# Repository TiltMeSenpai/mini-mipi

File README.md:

# mini-mipi
hi github actions (I just needed to kick the plotter script)

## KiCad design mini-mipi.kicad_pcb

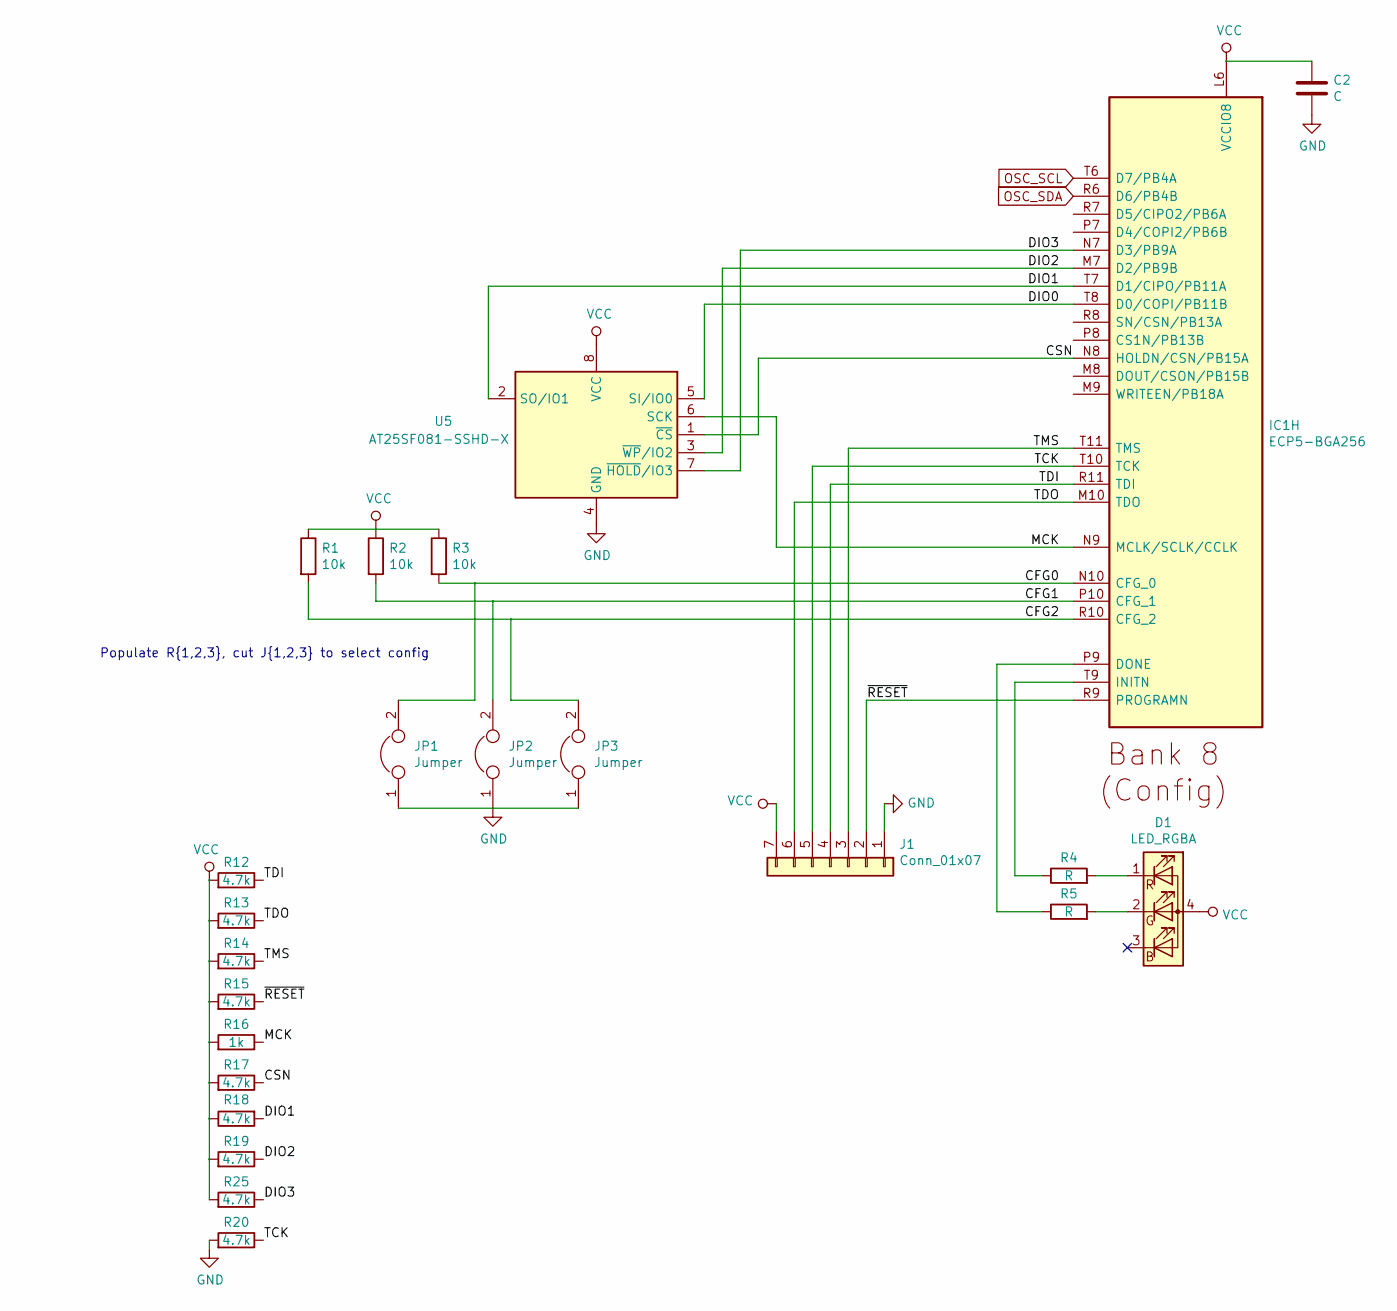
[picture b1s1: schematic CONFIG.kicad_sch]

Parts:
C2: C; C_0402_1005Metric
D1: LED_RGBA; LED_0404
IC1: ECP5-BGA256; BGA256C80P16X16_1400X1400X170; Manufacturer_Part_Number LFE5U-12F-6BG256C; Mouser Part Number 842-LFE5U12F6BG256C
J1: Conn_01x07; PinHeader_1x07_P2.54mm_Vertical
JP1, JP2, JP3: Jumper; SolderJumper-2_P1.3mm_Bridged_RoundedPad1.0x1.5mm
R1, R2, R3: 10k; R_0402_1005Metric
R4, R5: R; R_0402_1005Metric
R12, R13, R14, R15, R17, R18, R19, R20, R25: 4.7k; R_0402_1005Metric
R16: 1k; R_0402_1005Metric
U5: AT25SF081-SSHD-X; SOIC-8_5.275x5.275mm_P1.27mm

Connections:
/CONFIG/CFG0: IC1.N10 (CFG_0), JP1.2, R3.2
/CONFIG/CFG1: IC1.P10 (CFG_1), JP2.2, R2.2
/CONFIG/CFG2: IC1.R10 (CFG_2), JP3.2, R1.2
/CONFIG/CSN: IC1.N8 (HOLDN/CSN/PB15A), R17.1, U5.1 (~CS)
/CONFIG/DIO0: IC1.T8 (D0/COPI/PB11B), U5.5 (SI/IO0)
/CONFIG/DIO1: IC1.T7 (D1/CIPO/PB11A), R18.2, U5.2 (SO/IO1)
/CONFIG/DIO2: IC1.M7 (D2/PB9B), R19.1, U5.3 (~WP~/IO2)
/CONFIG/DIO3: IC1.N7 (D3/PB9A), R25.1, U5.7 (~HOLD~/IO3)
/CONFIG/MCK: IC1.N9 (MCLK/SCLK/CCLK), R16.1, U5.6 (SCK)
/CONFIG/TCK: IC1.T10 (TCK), J1.5, R20.1
/CONFIG/TDI: IC1.R11 (TDI), J1.4, R12.1
/CONFIG/TDO: IC1.M10 (TDO), J1.6, R13.1
/CONFIG/TMS: IC1.T11 (TMS), J1.3, R14.1
/CONFIG/~RESET: IC1.R9 (PROGRAMN), J1.2, R15.1
GND: C2.2, J1.1, JP1.1, JP2.1, JP3.1, R20.2, U5.4 (GND); also elsewhere on the board
unnamed: D1.1 (RK), R4.2
unnamed: D1.2 (GK), R5.2
unnamed: IC1.P9 (DONE), R5.1
unnamed: IC1.T9 (INITN), R4.1
OSC_SCL: IC1.T6 (D7/PB4A); also elsewhere on the board
OSC_SDA: IC1.R6 (D6/PB4B); also elsewhere on the board
VCC: C2.1, D1.4 (A), IC1.L6 (VCCIO8), J1.7, R1.1, R2.1, R3.1, R12.2, R13.2, R14.2, R15.2, R16.2, R17.2, R18.1, R19.2, R25.2, U5.8 (VCC); also elsewhere on the board

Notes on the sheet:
Populate R{1,2,3}, cut J{1,2,3} to select config

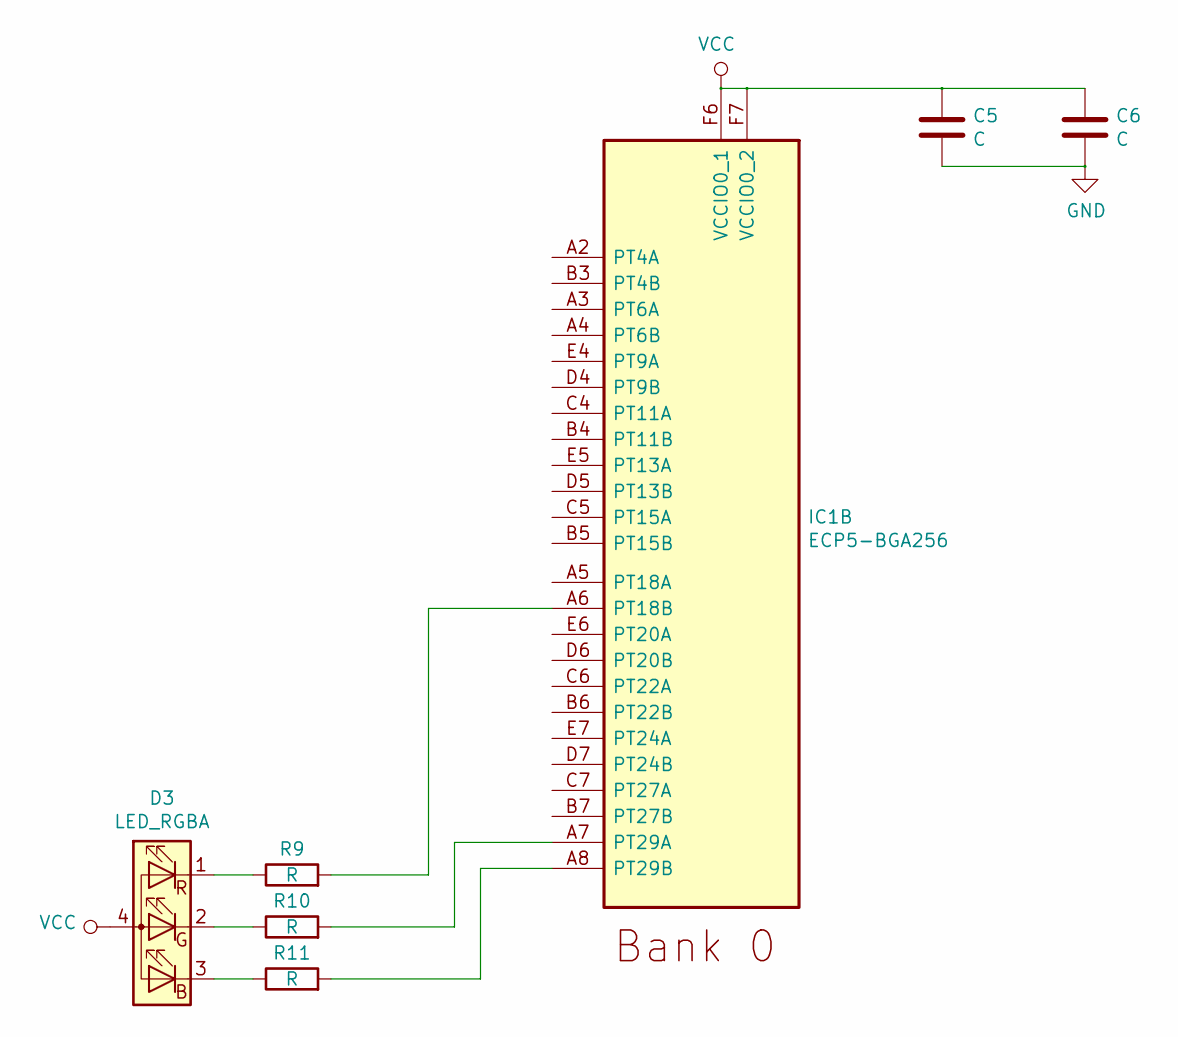
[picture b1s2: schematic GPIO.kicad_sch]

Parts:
C5, C6: C; C_0402_1005Metric
D3: LED_RGBA; LED_0404
IC1: ECP5-BGA256; BGA256C80P16X16_1400X1400X170; Manufacturer_Part_Number LFE5U-12F-6BG256C; Mouser Part Number 842-LFE5U12F6BG256C
R9, R10, R11: R; R_0402_1005Metric

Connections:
GND: C5.2, C6.2; also elsewhere on the board
unnamed: D3.1 (RK), R9.1
unnamed: D3.2 (GK), R10.1
unnamed: D3.3 (BK), R11.1
unnamed: IC1.A6 (PT18B), R9.2
unnamed: IC1.A7 (PT29A), R10.2
unnamed: IC1.A8 (PT29B), R11.2
VCC: C5.1, C6.1, D3.4 (A), IC1.F6 (VCCIO0_1), IC1.F7 (VCCIO0_2); also elsewhere on the board

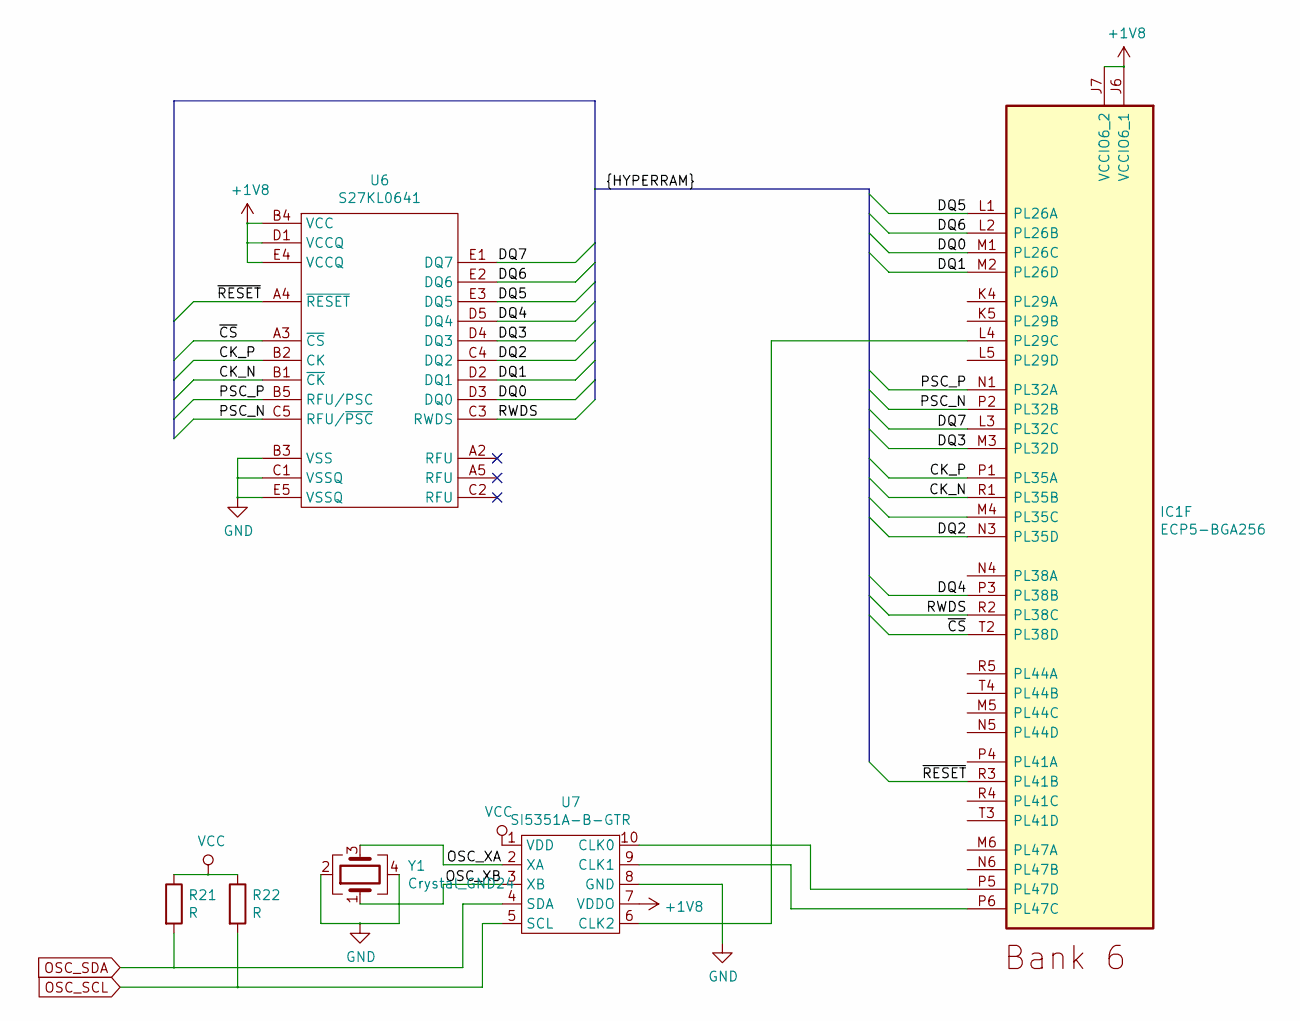
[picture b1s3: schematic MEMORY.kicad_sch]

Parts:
IC1: ECP5-BGA256; BGA256C80P16X16_1400X1400X170; Manufacturer_Part_Number LFE5U-12F-6BG256C; Mouser Part Number 842-LFE5U12F6BG256C
R21, R22: R; R_0402_1005Metric
U6: S27KL0641; BGA-24_5x5_6.0x8.0mm
U7: SI5351A-B-GTR; MSOP-10_3x3mm_P0.5mm
Y1: Crystal_GND24; Crystal_SMD_2016-4Pin_2.0x1.6mm

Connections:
+1V8: IC1.J6 (VCCIO6_1), IC1.J7 (VCCIO6_2), U6.B4 (VCC), U6.D1 (VCCQ), U6.E4 (VCCQ), U7.7 (VDDO); also elsewhere on the board
/MEMORY/CK_N: IC1.R1 (PL35B), U6.B1 (~CK)
/MEMORY/CK_P: IC1.P1 (PL35A), U6.B2 (CK)
/MEMORY/DQ0: IC1.M1 (PL26C), U6.D3 (DQ0)
/MEMORY/DQ1: IC1.M2 (PL26D), U6.D2 (DQ1)
/MEMORY/DQ2: IC1.N3 (PL35D), U6.C4 (DQ2)
/MEMORY/DQ3: IC1.M3 (PL32D), U6.D4 (DQ3)
/MEMORY/DQ4: IC1.P3 (PL38B), U6.D5 (DQ4)
/MEMORY/DQ5: IC1.L1 (PL26A), U6.E3 (DQ5)
/MEMORY/DQ6: IC1.L2 (PL26B), U6.E2 (DQ6)
/MEMORY/DQ7: IC1.L3 (PL32C), U6.E1 (DQ7)
/MEMORY/OSC_XA: U7.2 (XA), Y1.3
/MEMORY/OSC_XB: U7.3 (XB), Y1.1
/MEMORY/PSC_N: IC1.P2 (PL32B), U6.C5 (RFU/~PSC)
/MEMORY/PSC_P: IC1.N1 (PL32A), U6.B5 (RFU/PSC)
/MEMORY/RWDS: IC1.R2 (PL38C), U6.C3 (RWDS)
/MEMORY/~CS: IC1.T2 (PL38D), U6.A3 (~CS)
/MEMORY/~RESET: IC1.R3 (PL41B), U6.A4 (~RESET)
GND: U6.B3 (VSS), U6.C1 (VSSQ), U6.E5 (VSSQ), U7.8 (GND), Y1.2, Y1.4; also elsewhere on the board
unnamed: IC1.L4 (PL29C), U7.6 (CLK2)
unnamed: IC1.P5 (PL47D), U7.10 (CLK0)
unnamed: IC1.P6 (PL47C), U7.9 (CLK1)
OSC_SCL: R22.2, U7.5 (SCL); also elsewhere on the board
OSC_SDA: R21.2, U7.4 (SDA); also elsewhere on the board
VCC: R21.1, R22.1, U7.1 (VDD); also elsewhere on the board

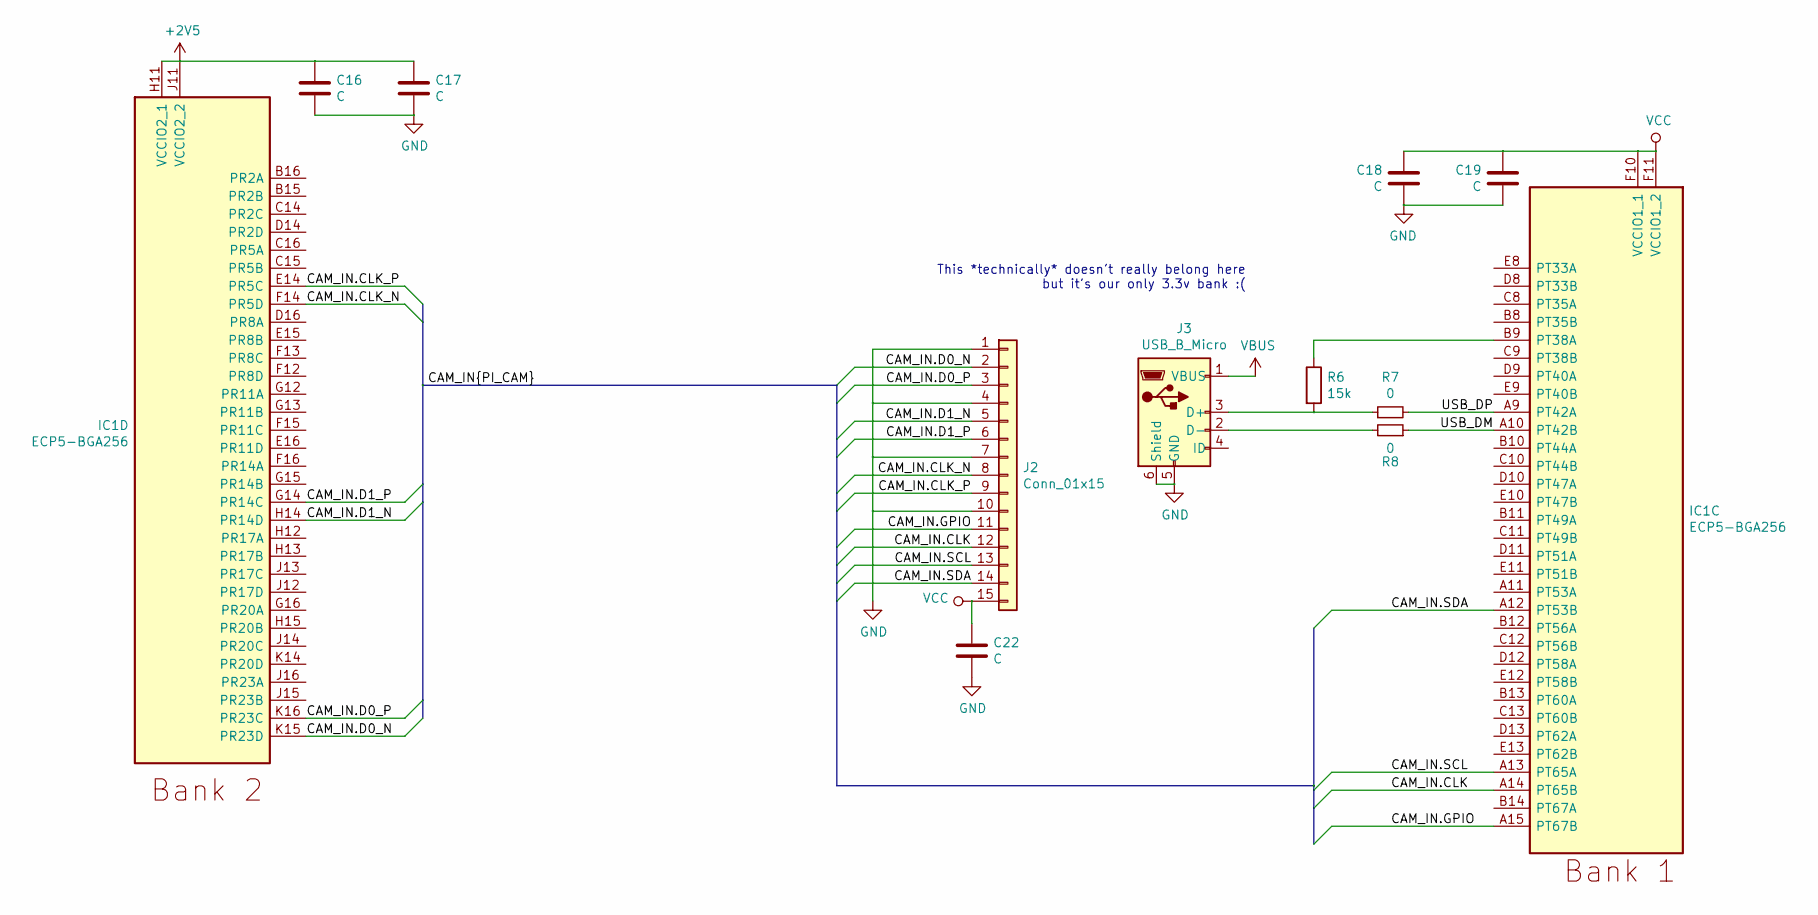
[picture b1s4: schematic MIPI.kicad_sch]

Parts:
C16, C17, C18, C19: C; C_0402_1005Metric
C22: C; C_0805_2012Metric
IC1: ECP5-BGA256; BGA256C80P16X16_1400X1400X170; Manufacturer_Part_Number LFE5U-12F-6BG256C; Mouser Part Number 842-LFE5U12F6BG256C
J2: Conn_01x15; AMPHENOL_SFW15R-1STE1LF
J3: USB_B_Micro; USB_Micro-B_Wuerth_629105150521
R6: 15k; R_0402_1005Metric
R7, R8: 0; R_0402_1005Metric

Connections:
+2V5: C16.1, C17.1, IC1.H11 (VCCIO2_1), IC1.J11 (VCCIO2_2); also elsewhere on the board
/MIPI/CAM_IN.CLK: IC1.A14 (PT65B), J2.12
/MIPI/CAM_IN.CLK_N: IC1.F14 (PR5D), J2.8
/MIPI/CAM_IN.CLK_P: IC1.E14 (PR5C), J2.9
/MIPI/CAM_IN.D0_N: IC1.K15 (PR23D), J2.2
/MIPI/CAM_IN.D0_P: IC1.K16 (PR23C), J2.3
/MIPI/CAM_IN.D1_N: IC1.H14 (PR14D), J2.5
/MIPI/CAM_IN.D1_P: IC1.G14 (PR14C), J2.6
/MIPI/CAM_IN.GPIO: IC1.A15 (PT67B), J2.11
/MIPI/CAM_IN.SCL: IC1.A13 (PT65A), J2.13
/MIPI/CAM_IN.SDA: IC1.A12 (PT53B), J2.14
/MIPI/USB_DM: IC1.A10 (PT42B), R8.1
/MIPI/USB_DP: IC1.A9 (PT42A), R7.2
GND: C16.2, C17.2, C18.2, C19.2, C22.2, J2.1, J2.4, J2.7, J2.10, J3.5 (GND), J3.6 (Shield); also elsewhere on the board
unnamed: IC1.B9 (PT38A), R6.1
unnamed: J3.2 (D-), R8.2
unnamed: J3.3 (D+), R6.2, R7.1
VBUS: J3.1 (VBUS); also elsewhere on the board
VCC: C18.1, C19.1, C22.1, IC1.F10 (VCCIO1_1), IC1.F11 (VCCIO1_2), J2.15; also elsewhere on the board

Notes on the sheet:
This *technically* doesn't really belong here but it's our only 3.3v bank :(

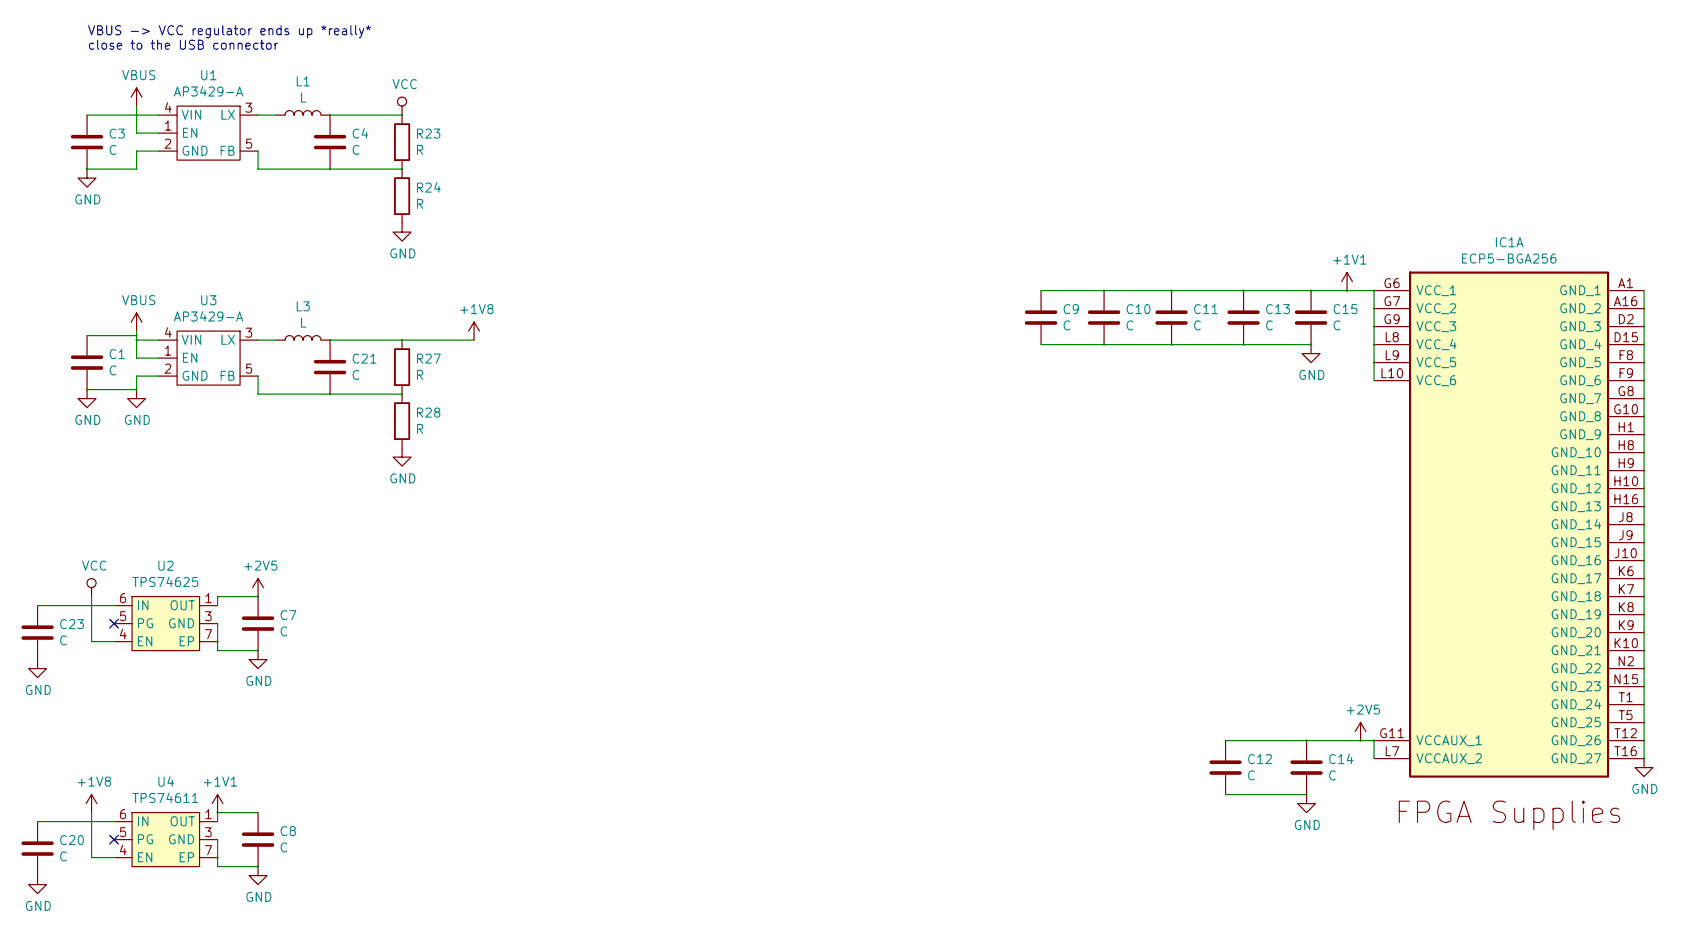
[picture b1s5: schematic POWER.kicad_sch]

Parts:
C1, C3, C7, C8, C20, C23: C; C_0805_2012Metric
C4, C9, C10, C11, C12, C13, C14, C15, C21: C; C_0402_1005Metric
IC1: ECP5-BGA256; BGA256C80P16X16_1400X1400X170; Manufacturer_Part_Number LFE5U-12F-6BG256C; Mouser Part Number 842-LFE5U12F6BG256C
L1, L3: L; L_1210_3225Metric
R23, R24, R27, R28: R; R_0402_1005Metric
U1, U3: AP3429-A; TSOT-23-5
U2: TPS74625; WSON-6-1EP_2x2mm_P0.65mm_EP1x1.6mm
U4: TPS74611; WSON-6-1EP_2x2mm_P0.65mm_EP1x1.6mm

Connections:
+1V1: C8.1, C9.1, C10.1, C11.1, C13.1, C15.1, IC1.G6 (VCC_1), IC1.G7 (VCC_2), IC1.G9 (VCC_3), IC1.L8 (VCC_4), IC1.L9 (VCC_5), IC1.L10 (VCC_6), U4.1 (OUT)
+1V8: C20.1, C21.1, L3.2, R27.1, U4.4 (EN), U4.6 (IN); also elsewhere on the board
+2V5: C7.1, C12.1, C14.1, IC1.G11 (VCCAUX_1), IC1.L7 (VCCAUX_2), U2.1 (OUT); also elsewhere on the board
GND: C1.2, C3.2, C7.2, C8.2, C9.2, C10.2, C11.2, C12.2, C13.2, C14.2, C15.2, C20.2, C23.2, IC1.A1 (GND_1), IC1.A16 (GND_2), IC1.D2 (GND_3), IC1.D15 (GND_4), IC1.F8 (GND_5), IC1.F9 (GND_6), IC1.G8 (GND_7), IC1.G10 (GND_8), IC1.H1 (GND_9), IC1.H8 (GND_10), IC1.H9 (GND_11), IC1.H10 (GND_12), IC1.H16 (GND_13), IC1.J8 (GND_14), IC1.J9 (GND_15), IC1.J10 (GND_16), IC1.K6 (GND_17), IC1.K7 (GND_18), IC1.K8 (GND_19), IC1.K9 (GND_20), IC1.K10 (GND_21), IC1.N2 (GND_22), IC1.N15 (GND_23), IC1.T1 (GND_24), IC1.T5 (GND_25), IC1.T12 (GND_26), IC1.T16 (GND_27), R24.2, R28.2, U1.2 (GND), U2.3 (GND), U2.7 (EP), U3.2 (GND), U4.3 (GND), U4.7 (EP); also elsewhere on the board
unnamed: C4.2, R23.2, R24.1, U1.5 (FB)
unnamed: C21.2, R27.2, R28.1, U3.5 (FB)
unnamed: L1.1, U1.3 (LX)
unnamed: L3.1, U3.3 (LX)
VBUS: C1.1, C3.1, U1.1 (EN), U1.4 (VIN), U3.1 (EN), U3.4 (VIN); also elsewhere on the board
VCC: C4.1, C23.1, L1.2, R23.1, U2.4 (EN), U2.6 (IN); also elsewhere on the board

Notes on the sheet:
VBUS -> VCC regulator ends up *really* close to the USB connector

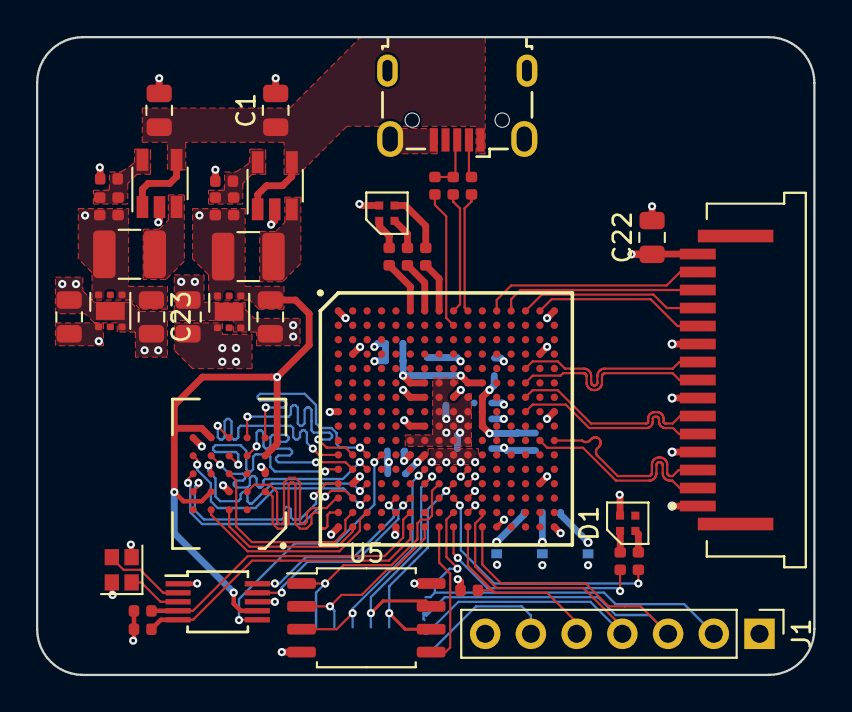
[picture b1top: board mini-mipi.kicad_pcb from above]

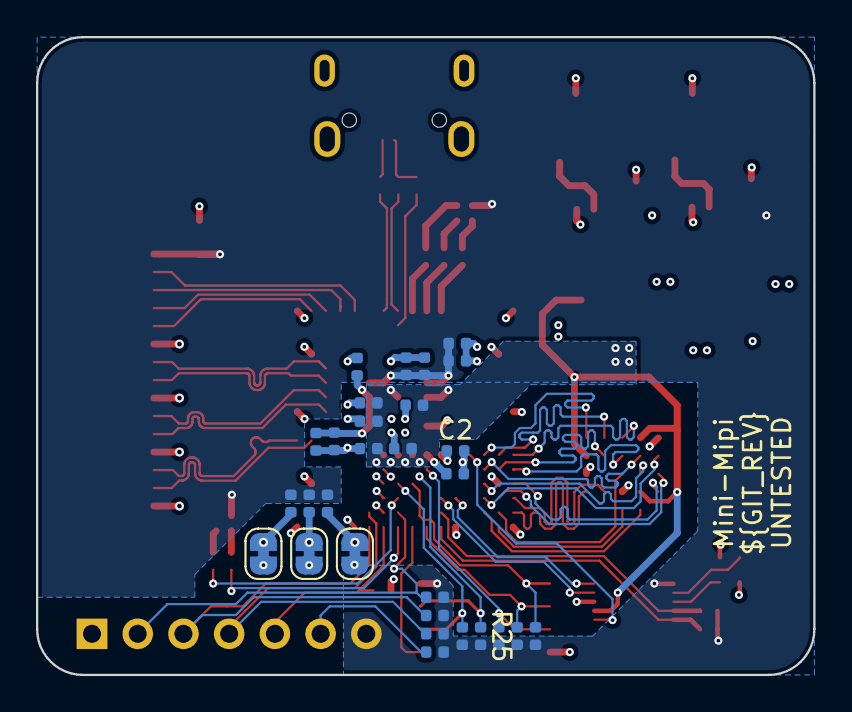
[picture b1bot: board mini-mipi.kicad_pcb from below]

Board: 4 copper layers, 43.2 x 35.4 mm, 69 parts (29 on the bottom side), 71 nets.

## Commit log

2020-07-14 Init
2020-07-14 Change box around voltage labels
2020-07-14 Change GIT_STRATEGY to clone
2020-07-14 Attempt to debug CI config
2020-07-14 Manually pull tags
2020-07-14 Add fix for missing tags
2020-07-14 Add Github Actions config
2020-07-14 Narrow down gerber artifact
2020-07-14 Revert e1fa5f9
2020-07-14 Add release config
2020-07-14 Fix artifact zip invocation
2020-07-15 Add semi-critical resistor values
2020-07-15 Debug missing tags
2020-07-15 Fix broken ci yml
2020-07-15 Checkout entire repo history (for tags)
2020-07-15 Remove debug step
2020-07-16 Add more pullup resistors
2020-07-16 Remember to save the schematic
2020-07-21 Change oscillator to SI5315, change RGB LED
2020-07-23 Change 1.8v and 3.3v regulators to buck for #2
2020-07-23 Improve decoupling
2020-07-31 Change debug header to 2.54mm standard
2020-08-06 Remember to add OHL-W License
2020-08-16 Remove SD card, relocate regulators
2020-08-26 Fix incorrect flash CSN pin
2023-06-30 Create README.md
    yeet
